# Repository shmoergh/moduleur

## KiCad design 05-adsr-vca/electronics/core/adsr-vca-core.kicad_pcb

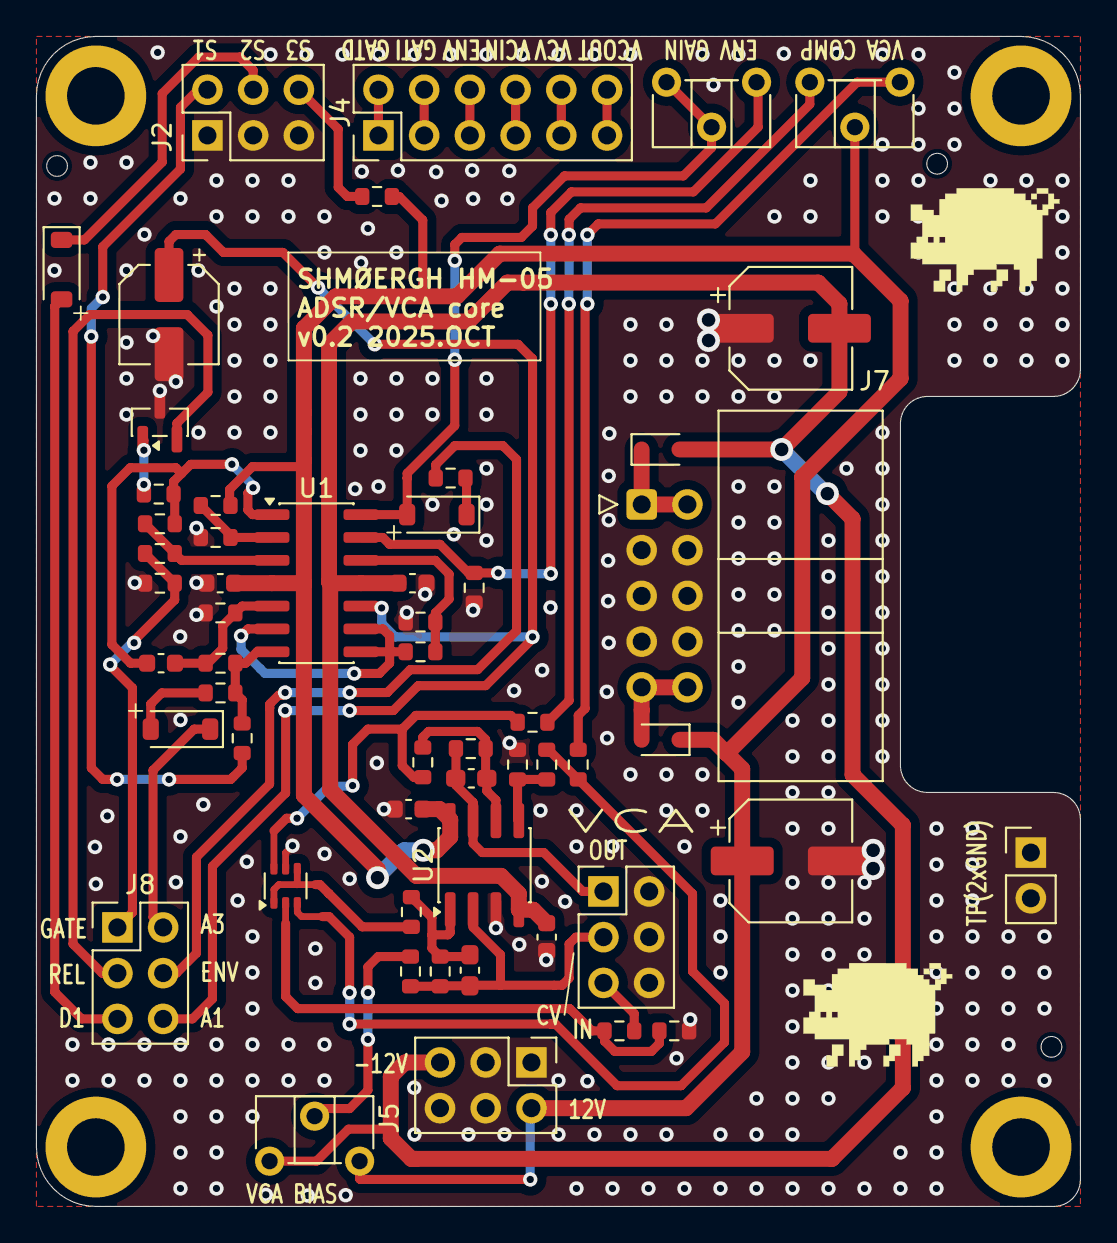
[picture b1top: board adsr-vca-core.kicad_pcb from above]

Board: 2 copper layers, 58.0 x 65.0 mm, 59 parts (0 on the bottom side), 45 nets.

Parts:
C1, C2, C5, C6: 100n; C_0603_1608Metric
C3: 10n; C_0603_1608Metric
C4: 10u; CP_Elec_5x5.4
C7, C8: 47p; C_0603_1608Metric_Pad1.08x0.95mm_HandSolder
C9, C10: 100u; CP_Elec_6.3x7.7
D1, D2, D3: 1N4148; D_SOD-123
D4, D5: 1N5817; D_SOD-323
H1, H2, H3, H4: MountingHole; MountingHole_3.2mm_M3_DIN965_Pad
J2, J3, J5, J8: Conn_02x03_Odd_Even; PinHeader_2x03_P2.54mm_Vertical
J4: Conn_02x06_Odd_Even; PinHeader_2x06_P2.54mm_Vertical
J6: Conn_01x02; PinHeader_1x02_P2.54mm_Vertical
J7: Conn_02x05_Odd_Even; IDC-Header_2x05_P2.54mm_Horizontal
Q1: BC857; SOT-23
Q3: BC847BS; SOT-363_SC-70-6
R1: 22k; R_0603_1608Metric
R2, R4, R9, R17: 1k; R_0603_1608Metric
R3, R14: 47k; R_0603_1608Metric
R5, R6, R7: 1M; R_0603_1608Metric
R8, R18, R22, R24: 100k; R_0603_1608Metric
R10, R12, R23, R25, R26: 10k; R_0603_1608Metric
R11: 4.7k; R_0603_1608Metric
R13: 15k; R_0603_1608Metric
R20: 220; R_0603_1608Metric
R21: 33k; R_0603_1608Metric
R27, R28: 470k; R_0603_1608Metric
R29: 200k; R_0603_1608Metric
RV_COMP1: 10k; Potentiometer_ACP_CA6-H2,5_Horizontal
RV_OUT_GAIN1: 100k; Potentiometer_ACP_CA6-H2,5_Horizontal
RV_VCA_BIAS1: 100k; Potentiometer_ACP_CA6-H2,5_Horizontal
U1: LM324; SOIC-14_3.9x8.7mm_P1.27mm
U2: TL072; SOIC-8_3.9x4.9mm_P1.27mm

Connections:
+12V: C1.1, C5.1, C9.1, D4.1 (K), J5.2, R1.2, R11.2, RV_COMP1.2, RV_VCA_BIAS1.3, U1.4 (V+), U2.8 (V+)
-12V: C2.2, C6.2, C10.2, D5.2 (A), J5.5, RV_VCA_BIAS1.1, U1.11 (V-), U2.4 (V-)
A1_D3_R3: C4.1, J8.6, U1.10 (+)
ATTACK_3: D1.1 (K), J8.2
DECAY_1: D2.2 (A), J8.5
ENV_OUT: J8.4, R17.1
GATE: J8.1, R3.2, R4.2
GND: C1.2, C2.1, C4.2, C5.2, C6.1, C9.2, C10.1, J2.1, J2.3, J2.5, J3.2, J3.4, J3.6, J5.1, J5.3, J5.4, J5.6, J6.1, J6.2, J7.3, J7.4, J7.5, J7.6, J7.7, J7.8, Q1.3 (C), Q3.5 (B2), R2.1, R3.1, R6.1, R13.1, R14.1, R20.1, R27.1, U2.3 (+)
unnamed: C3.1, R5.1, R8.2, U1.1
unnamed: C7.2, R21.2, R23.1, U2.1
unnamed: D1.2 (A), R9.1
unnamed: D3.2 (A), RV_OUT_GAIN1.2, RV_OUT_GAIN1.3, U1.14
unnamed: D3.1 (K), R17.2
unnamed: D4.2 (A), J7.9, J7.10
unnamed: D5.1 (K), J7.1, J7.2
unnamed: J4.1, J4.2
unnamed: J4.3, J4.4
unnamed: J4.5, J4.6
unnamed: J4.7, J4.8
unnamed: J4.9, J4.10
unnamed: J4.11, J4.12
unnamed: Q1.1 (B), R8.1
unnamed: Q3.2 (B1), R18.2, R20.2
unnamed: Q3.6 (C1), R22.1, R25.1
unnamed: Q3.1 (E1), Q3.4 (E2), R23.2
unnamed: Q3.3 (C2), R24.1, R26.1
unnamed: R7.1, R9.2, R10.1, U1.7
unnamed: R22.2, RV_COMP1.3
unnamed: R24.2, RV_COMP1.1
unnamed: R29.1, RV_VCA_BIAS1.2
unnamed: R4.1, R5.2, U1.3 (+)
unnamed: R1.1, R2.2, U1.2 (-)
unnamed: C3.2, R6.2, R7.2, U1.5 (+)
unnamed: R12.2, U1.6 (-), U1.8, U1.9 (-)
unnamed: R12.1, R13.2, U1.12 (+)
unnamed: R14.2, RV_OUT_GAIN1.1, U1.13 (-)
unnamed: R26.2, R27.2, U2.5 (+)
unnamed: C8.1, R25.2, R28.1, U2.6 (-)
RELEASE_1: J8.3, Q1.2 (E)
SUSTAIN_1: J2.2, R10.2
SUSTAIN_2: D2.1 (K), J2.4
SUSTAIN_3: J2.6, R11.1
VCA_CV: C7.1, J3.3, R21.1, R29.2, U2.2 (-)
VCA_IN: J3.5, R18.1
VCA_OUT: C8.2, J3.1, R28.2, U2.7

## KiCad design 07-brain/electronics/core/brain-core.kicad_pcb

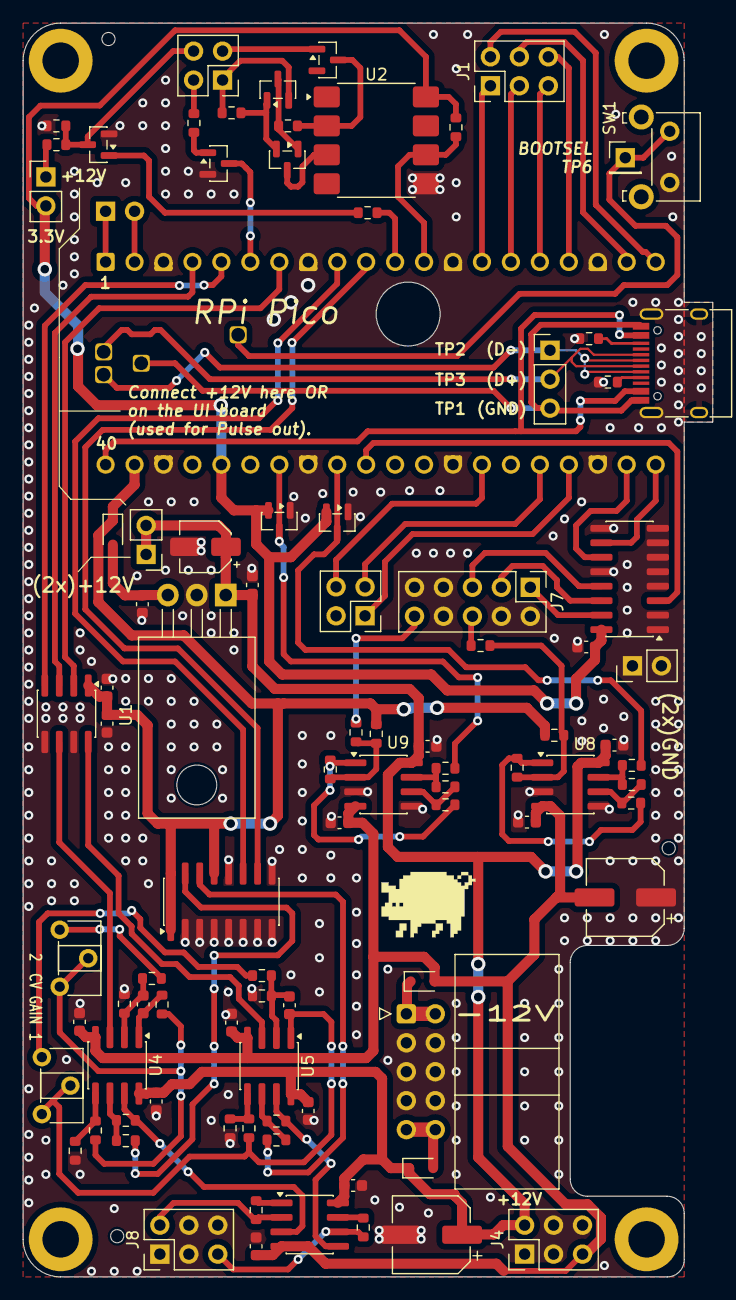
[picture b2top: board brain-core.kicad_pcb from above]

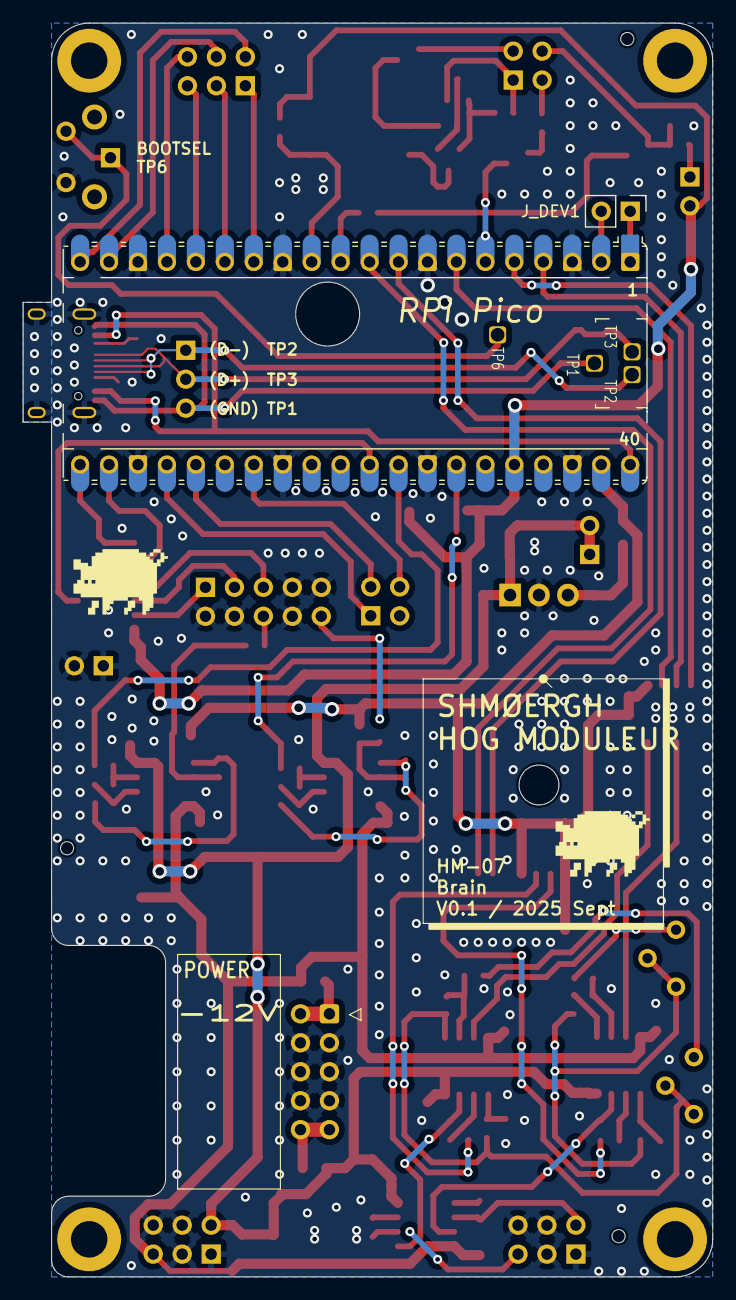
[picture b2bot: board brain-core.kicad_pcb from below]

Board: 2 copper layers, 60.5 x 110.0 mm, 98 parts (2 on the bottom side), 83 nets.

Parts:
C1: 10u; CP_Elec_4x5.4
C2: 330n; C_0603_1608Metric_Pad1.08x0.95mm_HandSolder
C3, C6, C7, C8, C9, C12, C13, C14, C15, C16, C17, C19, C20: 100n; C_0603_1608Metric
C4, C5: 100u; CP_Elec_6.3x7.7
C10, C11: 22p; C_0603_1608Metric
C18: 10u; C_0603_1608Metric
D1, D2, D3: 1N5817; D_SOD-323
D4: BAT54; SOT-23
D5, D6: BAT54S; SOT-23
H1, H2, H3, H4: MountingHole; MountingHole_3.2mm_M3_DIN965_Pad
J1, J4, J8: Conn_02x03_Odd_Even; PinHeader_2x03_P2.54mm_Vertical
J2, J3: Conn_02x02_Odd_Even; PinHeader_2x02_P2.54mm_Vertical
J5, J9, J10: Conn_01x02; PinHeader_1x02_P2.54mm_Vertical
J6: Conn_02x05_Odd_Even; IDC-Header_2x05_P2.54mm_Horizontal
J7: Conn_02x05_Odd_Even; PinHeader_2x05_P2.54mm_Vertical
J11: Conn_01x01; PinHeader_1x01_P2.54mm_Vertical
J13: Conn_01x03; PinHeader_1x03_P2.54mm_Vertical
J_DEV1: Conn_01x02; PinHeader_1x02_P2.54mm_Vertical
J_USB_C_EXTENSION1: USB_C_Receptacle_USB2.0_16P; USB_C_Receptacle_HRO_TYPE-C-31-M-12
Q1, Q3, Q6, Q7: MMBT3904; SOT-23
R1, R14, R15, R16, R17, R18, R19, R20, R21, R24, R26, R30, R31, R32, R33: 100k; R_0603_1608Metric
R2, R7: 3.3k; R_0603_1608Metric
R3: 10k; R_0603_1608Metric
R4: 7.5k; R_0603_1608Metric
R5: 2.2k; R_0603_1608Metric
R6: 120; R_0603_1608Metric
R8, R9: 47k; R_0603_1608Metric
R10, R11: 62k; R_0603_1608Metric
R12, R22, R23, R34, R35: 1k; R_0603_1608Metric
R25, R27: 120k; R_0603_1608Metric
R28, R29: 33k; R_0603_1608Metric
R36, R37: 5.1k; R_0603_1608Metric
RV_CV_GAIN1, RV_CV_GAIN2: 10k; Potentiometer_ACP_CA6-H2,5_Horizontal
SW1: SW_SPST; SW_Tactile_SKHH_Angled
U1: LM7805_TO220; TO-220-3_Horizontal_TabDown
U2: 6N137; SOP-8_6.605x9.655mm_P2.54mm
U3: Pico; RaspberryPi_Pico_Common_Unspecified
U4, U5, U8, U9, U11: TL072; SOIC-8_3.9x4.9mm_P1.27mm
U6: MCP4822; SOIC-8_3.9x4.9mm_P1.27mm
U7: 74HC4053B; SOIC-16_3.9x9.9mm_P1.27mm
U10: 74HC4051; SOIC-16_3.9x9.9mm_P1.27mm

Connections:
+3.3V: C16.1, D5.2 (K), D6.2 (K), J10.2, R7.2, U2.8 (VCC), U3.36 (3V3), U10.16 (VCC)
+5V: C17.1, C18.1, D1.1 (K), R24.1, R26.1, U3.39 (VSYS), U6.1 (Vdd), U7.1 (B1), U7.13 (A1), U7.16 (VDD)
+12V: C1.1, C2.1, C4.1, C6.1, C8.1, C12.1, C14.1, C19.1, D2.1 (K), J4.2, J9.1, J9.2, J10.1, R3.2, U1.1 (VI), U4.8 (V+), U5.8 (V+), U8.8 (V+), U9.8 (V+), U11.8 (V+)
-12V: C5.2, C7.2, C9.2, C13.2, C15.2, C20.2, D3.2 (A), J4.5, U4.4 (V-), U5.4 (V-), U8.4 (V-), U9.4 (V-), U11.4 (V-)
/GPIO_2: U3.4 (GPIO2), U6.3 (SCK)
/GPIO_3: U3.5 (GPIO3), U6.4 (SDI)
/GPIO_4: Q1.3 (C), U3.6 (GPIO4)
/GPIO_5: U3.7 (GPIO5), U6.2 (~CS)
/GPIO_6: U3.9 (GPIO6), U7.11 (S1)
/GPIO_7: U3.10 (GPIO7), U7.10 (S2)
/GPIO_8: R2.1, U3.11 (GPIO8)
/GPIO_9: R7.1, U2.6 (VO), U3.12 (GPIO9)
/GPIO_16: U3.22 (GPIO17), U10.11 (S0)
/GPIO_17: U3.21 (GPIO16), U10.10 (S1)
/GPIO_26: U3.31 (GPIO26_ADC0), U10.3 (A)
/GPIO_27: D5.3 (COM), R34.2, U3.32 (GPIO27_ADC1)
/GPIO_28: D6.3 (COM), R35.2, U3.34 (GPIO28_ADC2)
/MCU/TP1: J13.3, J_USB_C_EXTENSION1.A1 (GND), J_USB_C_EXTENSION1.A12 (GND), J_USB_C_EXTENSION1.B1 (GND), J_USB_C_EXTENSION1.B12 (GND), U3.44 (TP1)
/MCU/TP2: J13.1, J_USB_C_EXTENSION1.A7 (D-), J_USB_C_EXTENSION1.B7 (D-), U3.45 (TP2)
/MCU/TP3: J13.2, J_USB_C_EXTENSION1.A6 (D+), J_USB_C_EXTENSION1.B6 (D+), U3.46 (TP3)
/MCU/TP6: J11.1, SW1.1 (A), U3.47 (TP6)
/MCU/UART_RX: J_DEV1.2, U3.2 (GPIO1)
/MCU/UART_TX: J_DEV1.1, U3.1 (GPIO0)
AUDIO_CV_IN_1: J7.6, R25.1
AUDIO_CV_IN_2: J7.10, R27.1
AUDIO_CV_OUT_1: J8.5, R23.2, U11.6 (-)
AUDIO_CV_OUT_2: J8.2, R22.2, U11.2 (-)
BTN_1: J3.1, U3.24 (GPIO18)
BTN_2: J3.3, U3.25 (GPIO19)
BTN_LED_1: J3.4, U3.27 (GPIO21)
GND: C1.2, C2.2, C3.2, C4.2, C5.1, C6.2, C7.1, C8.2, C9.1, C12.2, C13.1, C14.2, C15.1, C16.2, C17.2, C18.2, C19.2, C20.1, D5.1 (A), D6.1 (A), J4.1, J4.3, J4.4, J4.6, J5.1, J5.2, J6.3, J6.4, J6.5, J6.6, J6.7, J6.8, J7.2, J7.4, J7.7, J7.8, J7.9, J8.1, J8.3, J8.4, J8.6, J_USB_C_EXTENSION1.S1 (SHIELD), Q1.2 (E), Q3.2 (E), R4.1, R8.1, R9.1, R16.1, R17.1, R36.2, R37.2, SW1.2 (B), U1.2 (GND), U2.5 (GND), U3.3 (GND), U3.8 (GND), U3.13 (GND), U3.18 (GND), U3.23 (GND), U3.28 (GND), U3.33 (AGND), U3.38 (GND), U6.5 (~LDAC), U6.7 (Vss), U7.2 (B0), U7.3 (C1), U7.4 (C), U7.5 (C0), U7.6 (INH), U7.7 (VEE), U7.8 (VSS), U7.9 (S3), U7.12 (A0), U8.3 (+), U8.5 (+), U9.3 (+), U9.5 (+), U10.1 (A4), U10.2 (A6), U10.4 (A7), U10.5 (A5), U10.6 (~E), U10.7 (VEE), U10.8 (GND), U10.9 (S2), U10.12 (A3)
LED_1: J1.1, U3.14 (GPIO10)
LED_2: J1.3, U3.15 (GPIO11)
LED_3: J1.5, U3.16 (GPIO12)
LED_4: J1.6, U3.17 (GPIO13)
LED_5: J1.4, U3.19 (GPIO14)
LED_6: J1.2, U3.20 (GPIO15)
MIDI_4R: D4.1 (A), J2.3
MIDI_5T: J2.1, Q6.2 (E), R6.1
unnamed: C10.2, R12.1, U4.1
unnamed: C11.2, R15.1, RV_CV_GAIN1.2, RV_CV_GAIN1.3, U5.1
unnamed: C3.1, D1.2 (A), U1.3 (VO)
unnamed: D2.2 (A), J6.9, J6.10
unnamed: D3.1 (K), J6.1, J6.2
unnamed: D4.3 (K), R5.2, U2.2 (A)
unnamed: J_USB_C_EXTENSION1.A5 (CC1), R36.1
unnamed: J_USB_C_EXTENSION1.B5 (CC2), R37.1
unnamed: Q1.1 (B), R1.2
unnamed: Q3.1 (B), R2.2
unnamed: Q6.1 (B), Q7.2 (E), R6.2
unnamed: Q6.3 (C), Q7.1 (B), R5.1
unnamed: Q7.3 (C), U2.3 (C)
unnamed: R10.2, RV_CV_GAIN2.1
unnamed: R11.2, RV_CV_GAIN1.1
unnamed: R12.2, R14.1, RV_CV_GAIN2.2, RV_CV_GAIN2.3
unnamed: R22.1, U11.1
unnamed: R23.1, U11.7
unnamed: R28.2, R30.1, U8.1
unnamed: R29.2, R31.1, U9.1
unnamed: R32.2, R34.1, U8.7
unnamed: R33.2, R35.1, U9.7
unnamed: J_USB_C_EXTENSION1.A4 (VBUS), J_USB_C_EXTENSION1.A9 (VBUS), J_USB_C_EXTENSION1.B4 (VBUS), J_USB_C_EXTENSION1.B9 (VBUS), U3.40 (VBUS)
unnamed: U4.3 (+), U6.6 (VB)
unnamed: C10.1, R8.2, R10.1, U4.2 (-)
unnamed: R14.2, R16.2, U4.5 (+)
unnamed: R19.1, R20.1, U4.6 (-)
unnamed: U5.3 (+), U6.8 (VA)
unnamed: C11.1, R9.2, R11.1, U5.2 (-)
unnamed: R15.2, R17.2, U5.5 (+)
unnamed: R18.2, R21.1, U5.6 (-)
unnamed: R18.1, U7.14 (A)
unnamed: R19.2, U7.15 (B)
unnamed: R24.2, R25.2, R28.1, U8.2 (-)
unnamed: R30.2, R32.1, U8.6 (-)
unnamed: R26.2, R27.2, R29.1, U9.2 (-)
unnamed: R31.2, R33.1, U9.6 (-)
unnamed: R20.2, U4.7, U11.3 (+)
unnamed: R21.2, U5.7, U11.5 (+)
POT_1: J7.5, U10.13 (A0)
POT_2: J7.3, U10.14 (A1)
POT_3: J7.1, U10.15 (A2)
PULSE_IN: J2.2, R1.1
PULSE_OUT: J2.4, Q3.3 (C), R3.1, R4.2

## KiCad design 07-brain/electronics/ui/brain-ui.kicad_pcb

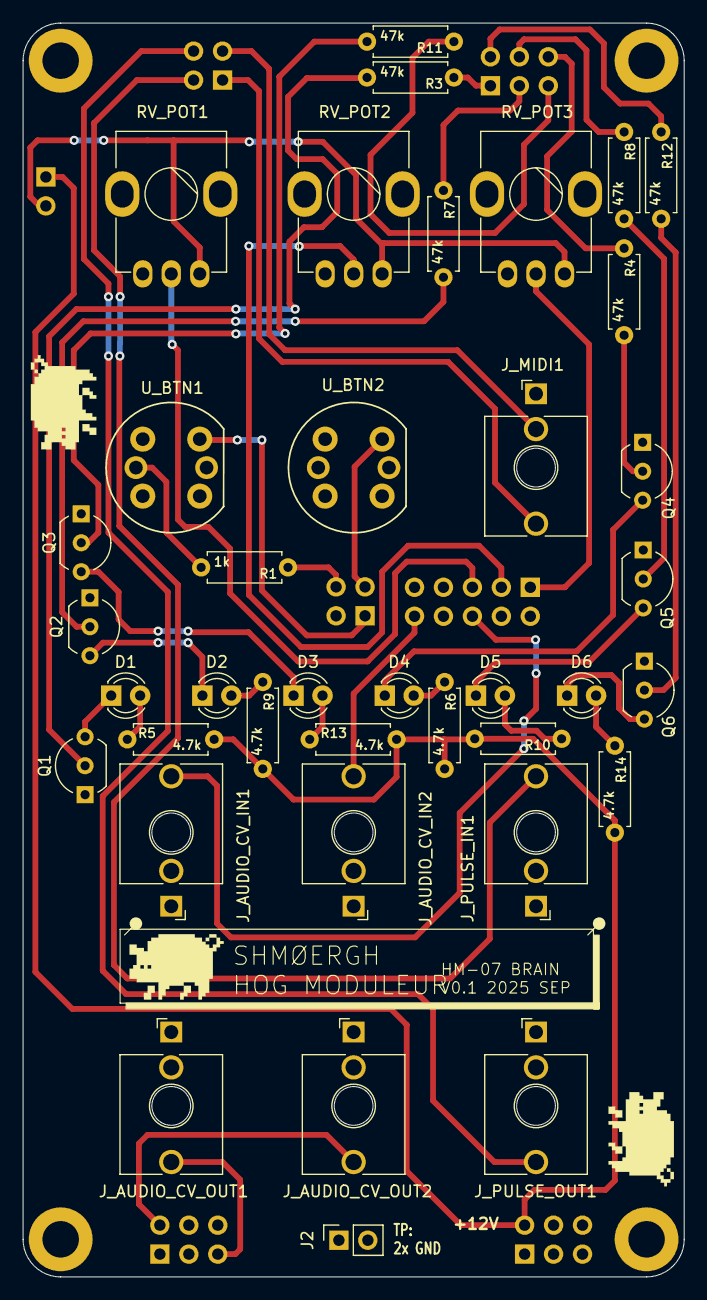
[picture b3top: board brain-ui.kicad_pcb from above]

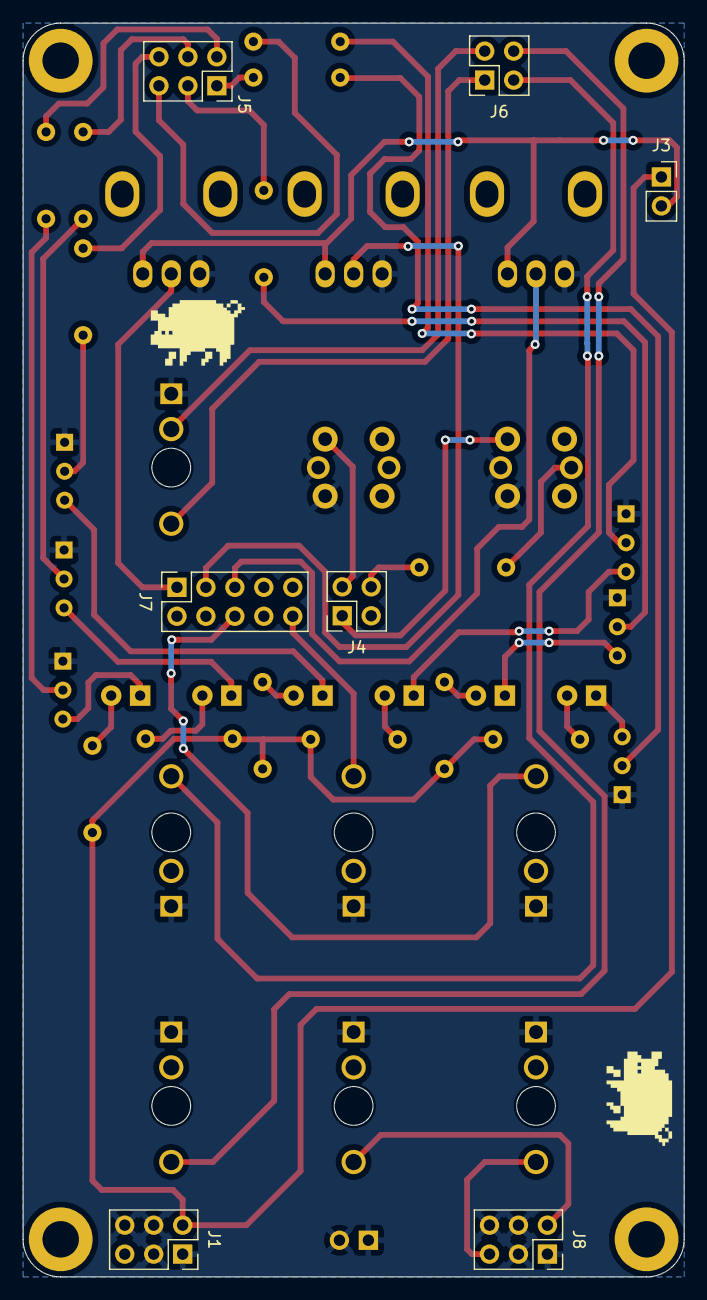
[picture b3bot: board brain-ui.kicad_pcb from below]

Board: 2 copper layers, 58.0 x 110.0 mm, 49 parts (7 on the bottom side), 42 nets.

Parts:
D1, D2, D3, D4, D5, D6: LED; LED_D3.0mm
H1, H2, H3, H4: MountingHole; MountingHole_3.2mm_M3_DIN965_Pad
J1, J5, J8: Conn_02x03_Odd_Even; PinSocket_2x03_P2.54mm_Vertical
J2, J3: Conn_01x02; PinSocket_1x02_P2.54mm_Vertical
J4, J6: Conn_02x02_Odd_Even; PinSocket_2x02_P2.54mm_Vertical
J7: Conn_02x05_Odd_Even; PinSocket_2x05_P2.54mm_Vertical
J_AUDIO_CV_IN1, J_AUDIO_CV_IN2: PJ398SM; Jack_3.5mm_QingPu_WQP-PJ398SM_Vertical_CircularHoles
J_AUDIO_CV_OUT1, J_AUDIO_CV_OUT2: PJ398SM; Jack_3.5mm_QingPu_WQP-PJ398SM_Vertical_CircularHoles
J_MIDI1: PJ398SM-STEREO; Jack_3.5mm_QingPu_WQP-PJ398SM_Vertical_CircularHoles
J_PULSE_IN1: PJ398SM; Jack_3.5mm_QingPu_WQP-PJ398SM_Vertical_CircularHoles
J_PULSE_OUT1: PJ398SM; Jack_3.5mm_QingPu_WQP-PJ398SM_Vertical_CircularHoles
Q1, Q2, Q3, Q4, Q5, Q6: 2N3904; TO-92_Inline_Wide
R1: 1k; R_Axial_DIN0207_L6.3mm_D2.5mm_P7.62mm_Horizontal
R3, R4, R7, R8, R11, R12: 47k; R_Axial_DIN0207_L6.3mm_D2.5mm_P7.62mm_Horizontal
R5, R6, R9, R10, R13, R14: 4.7k; R_Axial_DIN0207_L6.3mm_D2.5mm_P7.62mm_Horizontal
RV_POT1, RV_POT2, RV_POT3: 100k; Potentiometer_Bourns_Single-PTV09A
U_BTN1: SW_SPST_Push_LED; SPST_Circular_Pushbutton_LED
U_BTN2: SW_SPST_Push; SPST_Circular_Pushbutton_LED

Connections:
+3.3V: J3.2, RV_POT1.3, RV_POT2.3, RV_POT3.3
+12V: J1.2, J3.1, R5.2, R6.2, R9.2, R10.2, R13.2, R14.2
AUDIO_CV_IN_1: J7.6, J_AUDIO_CV_IN1.T
AUDIO_CV_IN_2: J7.10, J_AUDIO_CV_IN2.T
AUDIO_CV_OUT_1: J8.5, J_AUDIO_CV_OUT1.T
AUDIO_CV_OUT_2: J8.2, J_AUDIO_CV_OUT2.T
BTN_1: J4.1, U_BTN1.2
BTN_2: J4.3, U_BTN2.2
BTN_LED_1: J4.4, R1.1
GND: J1.1, J1.3, J1.4, J1.6, J2.1, J2.2, J8.1, J8.3, J8.4, J8.6, J_AUDIO_CV_IN1.S, J_AUDIO_CV_IN2.S, J_AUDIO_CV_OUT1.S, J_AUDIO_CV_OUT2.S, J_MIDI1.S, J_PULSE_IN1.S, J_PULSE_OUT1.S, Q1.1 (E), Q2.1 (E), Q3.1 (E), Q4.1 (E), Q5.1 (E), Q6.1 (E), RV_POT1.1, RV_POT2.1, RV_POT3.1, U_BTN1.4, U_BTN1.L2, U_BTN2.4, U_BTN2.L2
LED_1: J5.1, R3.1
LED_2: J5.3, R7.1
LED_3: J5.5, R11.1
LED_4: J5.6, R4.1
LED_5: J5.4, R8.1
LED_6: J5.2, R12.1
MIDI_4R: J6.3, J_MIDI1.TN
MIDI_5T: J6.1, J_MIDI1.T
unnamed: D1.2 (A), R5.1
unnamed: D1.1 (K), Q1.3 (C)
unnamed: D2.2 (A), R9.1
unnamed: D2.1 (K), Q2.3 (C)
unnamed: D3.2 (A), R13.1
unnamed: D3.1 (K), Q3.3 (C)
unnamed: D4.2 (A), R6.1
unnamed: D4.1 (K), Q4.3 (C)
unnamed: D5.2 (A), R10.1
unnamed: D5.1 (K), Q5.3 (C)
unnamed: D6.2 (A), R14.1
unnamed: D6.1 (K), Q6.3 (C)
unnamed: Q1.2 (B), R3.2
unnamed: Q2.2 (B), R7.2
unnamed: Q3.2 (B), R11.2
unnamed: Q4.2 (B), R4.2
unnamed: Q5.2 (B), R8.2
unnamed: Q6.2 (B), R12.2
unnamed: R1.2, U_BTN1.L1
POT_1: J7.5, RV_POT1.2
POT_2: J7.3, RV_POT2.2
POT_3: J7.1, RV_POT3.2
PULSE_IN: J6.2, J_PULSE_IN1.T
PULSE_OUT: J6.4, J_PULSE_OUT1.T

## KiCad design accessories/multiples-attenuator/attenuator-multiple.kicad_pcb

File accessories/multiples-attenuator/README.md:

# Multiples x Attenuator

Super simple passive module that combines a 1 -> 4 multiples with 2x attenuator. You can use linear or logarithmic pots if you want different attenuation curve.

Status: UNTESTED

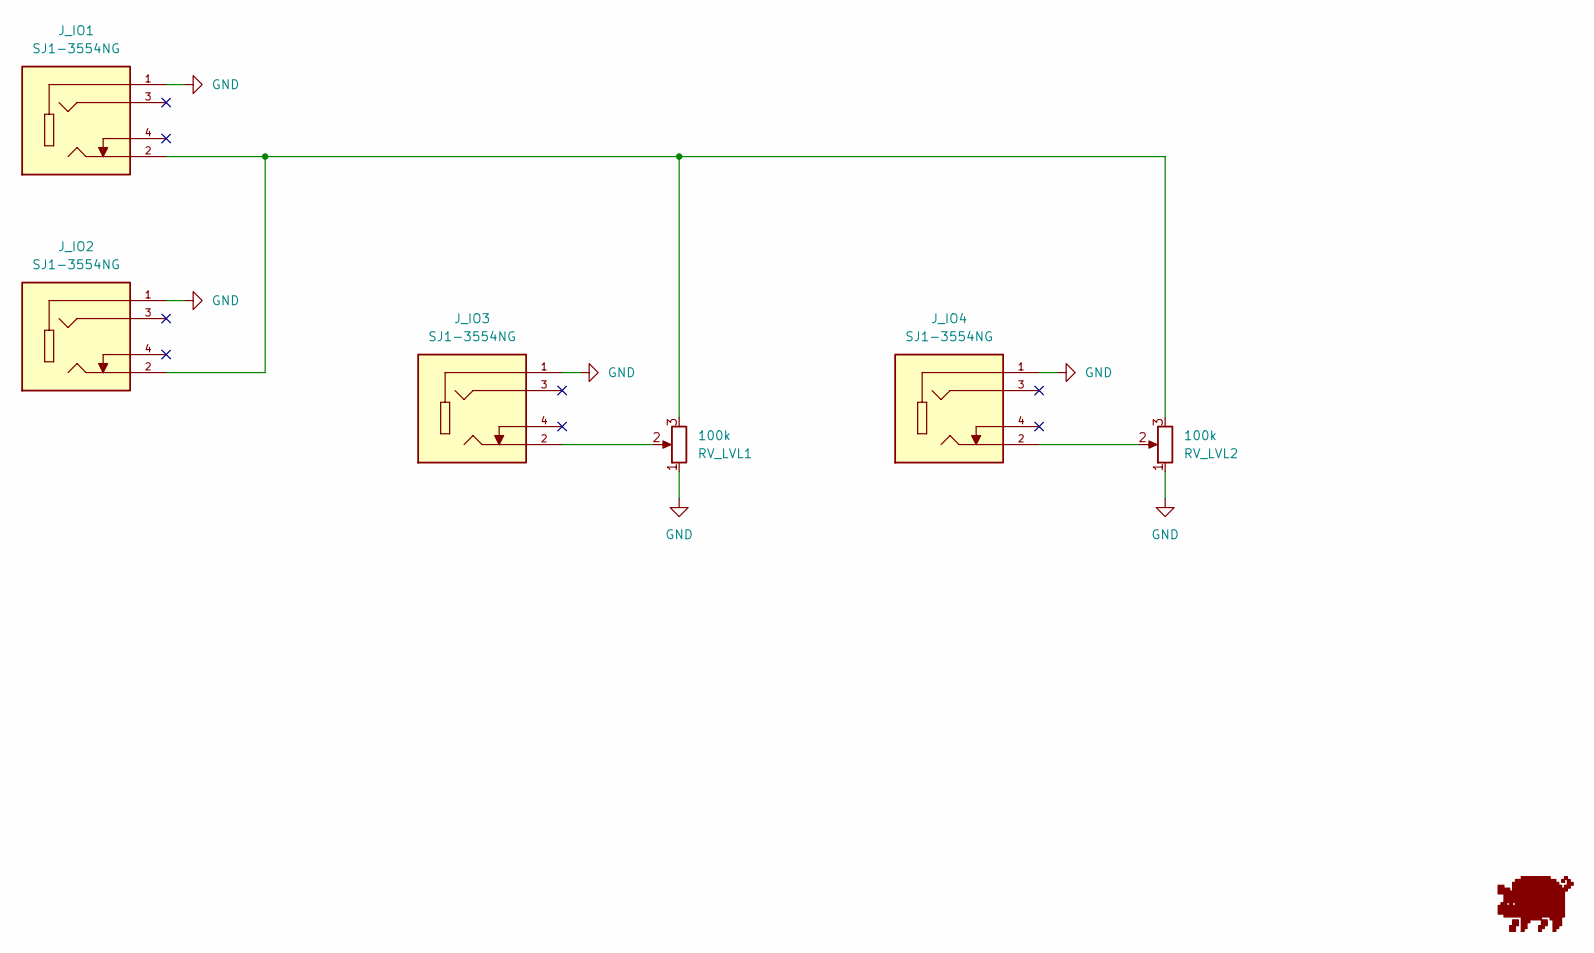
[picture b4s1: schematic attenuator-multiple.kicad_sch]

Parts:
J_IO1, J_IO2, J_IO3, J_IO4: SJ1-3554NG; CUI_SJ1-3554NG; PARTREV 1.05
RV_LVL1, RV_LVL2: 100k; Potentiometer_Bourns_Single-PTV09A; Part no. 652-PTV09A4025UB104
U1: Gyeszno

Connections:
GND: J_IO1.1, J_IO2.1, J_IO3.1, J_IO4.1, RV_LVL1.1, RV_LVL2.1
unnamed: J_IO1.2, J_IO2.2, RV_LVL1.3, RV_LVL2.3
unnamed: J_IO3.2, RV_LVL1.2
unnamed: J_IO4.2, RV_LVL2.2

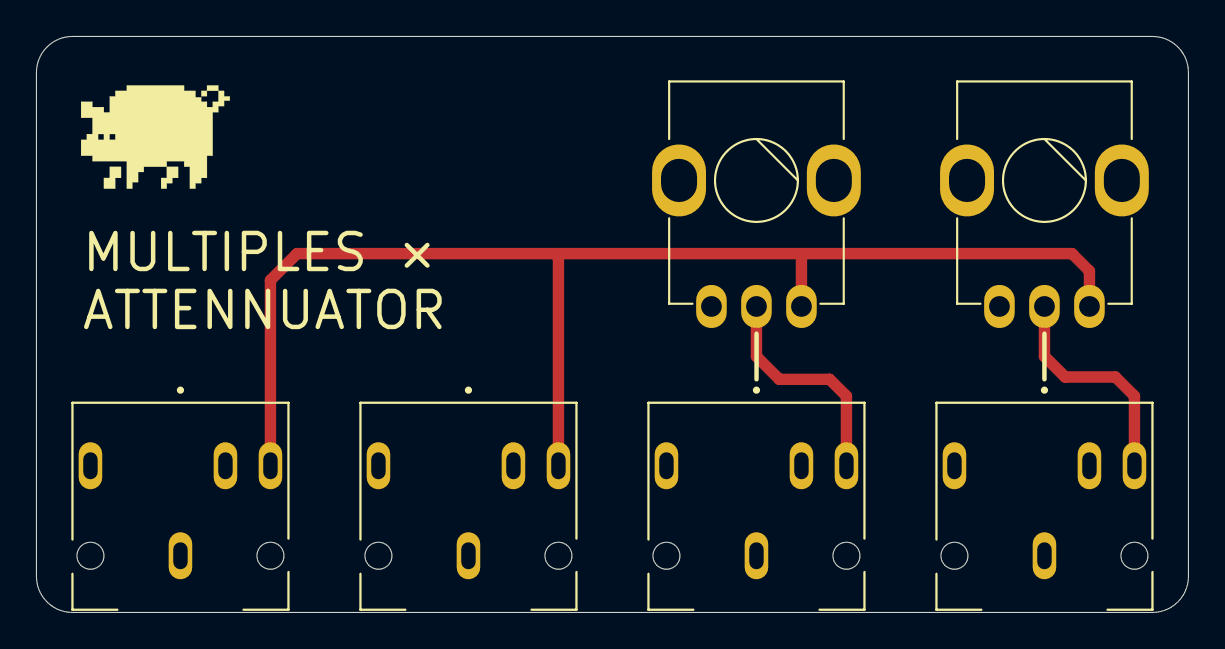
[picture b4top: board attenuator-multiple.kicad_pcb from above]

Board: 2 copper layers, 64.0 x 32.0 mm, 7 parts (0 on the bottom side), 4 nets.
